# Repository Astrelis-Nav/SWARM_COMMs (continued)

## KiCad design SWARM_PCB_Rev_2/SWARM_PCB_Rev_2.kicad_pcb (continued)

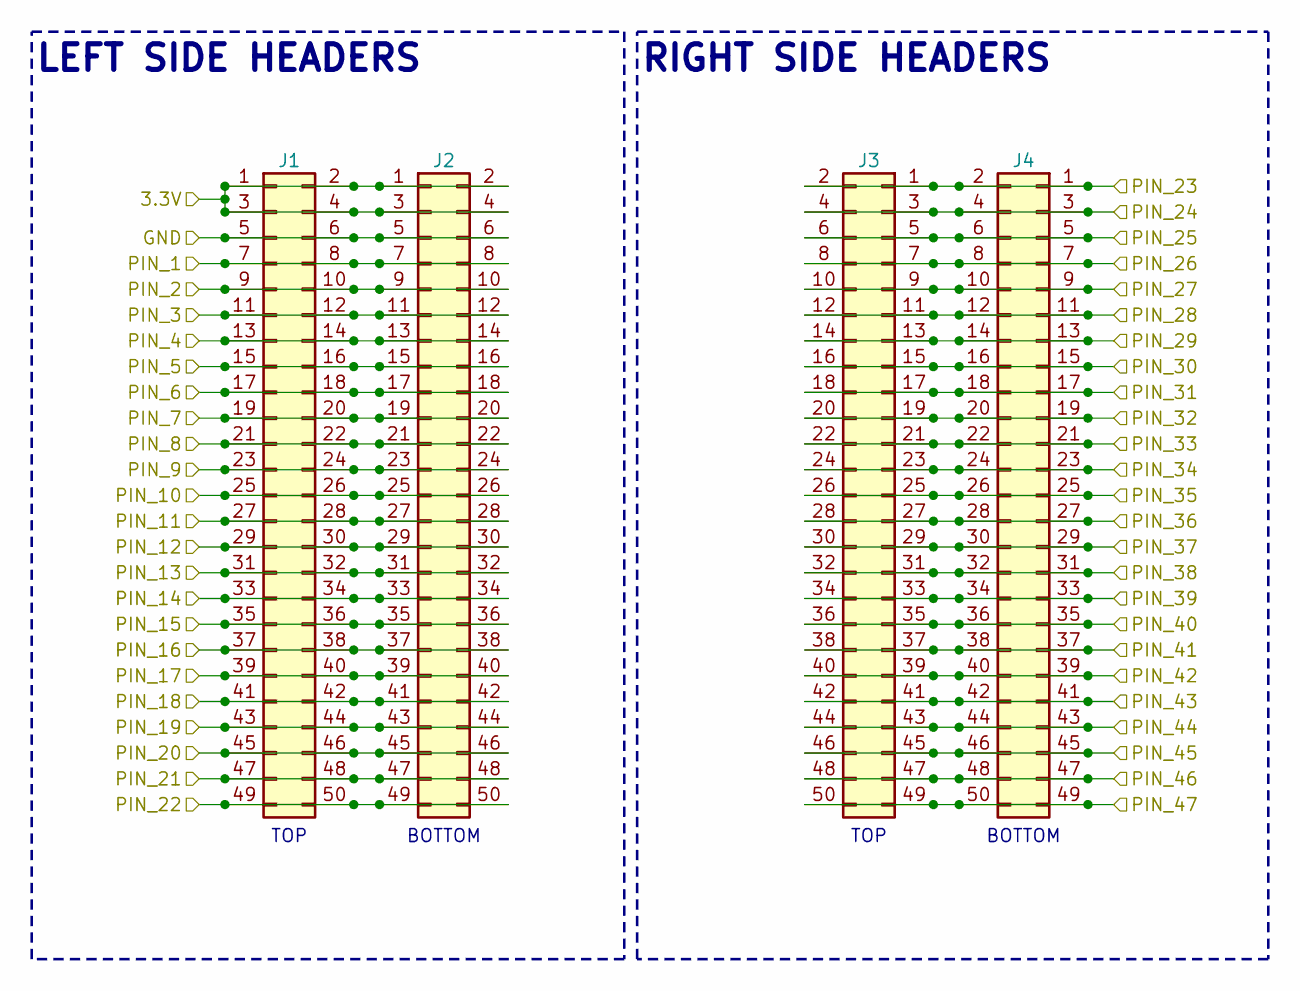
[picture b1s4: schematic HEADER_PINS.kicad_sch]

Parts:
J1: Conn_02x25_Odd_Even; HIROSE_DF40C-50DP-0.4V_51_
J2, J3, J4: Conn_02x25_Odd_Even; HIROSE_DF40C-50DP-0.4V_51_; MPN DF40C-50DP-0.4V(51)

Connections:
+3.3V_CONTROL: J1.1, J1.2, J1.3, J1.4, J2.1, J2.2, J2.3, J2.4; also elsewhere on the board
/CONTROL/ADC1_IN0: J3.45, J3.46, J4.45, J4.46; also elsewhere on the board
/CONTROL/ADC1_IN1: J3.47, J3.48, J4.47, J4.48; also elsewhere on the board
/CONTROL/ADC1_IN2: J3.49, J3.50, J4.49, J4.50; also elsewhere on the board
/CONTROL/ADC1_IN3: J3.37, J3.38, J4.37, J4.38; also elsewhere on the board
/CONTROL/GPIO_0: J3.1, J3.2, J4.1, J4.2; also elsewhere on the board
/CONTROL/GPIO_1: J3.3, J3.4, J4.3, J4.4; also elsewhere on the board
/CONTROL/GPIO_6: J3.5, J3.6, J4.5, J4.6; also elsewhere on the board
/CONTROL/GPIO_7: J3.7, J3.8, J4.7, J4.8; also elsewhere on the board
/CONTROL/GPIO_8: J3.9, J3.10, J4.9, J4.10; also elsewhere on the board
/CONTROL/GPIO_9: J3.11, J3.12, J4.11, J4.12; also elsewhere on the board
/CONTROL/GPIO_10: J3.13, J3.14, J4.13, J4.14; also elsewhere on the board
/CONTROL/GPIO_11: J3.15, J3.16, J4.15, J4.16; also elsewhere on the board
/CONTROL/GPIO_12: J3.17, J3.18, J4.17, J4.18; also elsewhere on the board
/CONTROL/GPIO_13: J3.19, J3.20, J4.19, J4.20; also elsewhere on the board
/CONTROL/GPIO_14: J3.21, J3.22, J4.21, J4.22; also elsewhere on the board
/CONTROL/GPIO_15: J3.23, J3.24, J4.23, J4.24; also elsewhere on the board
/CONTROL/GPIO_21: J1.39, J1.40, J2.39, J2.40; also elsewhere on the board
/CONTROL/GPIO_22: J1.13, J1.14, J2.13, J2.14; also elsewhere on the board
/CONTROL/GPIO_26: J1.11, J1.12, J2.11, J2.12; also elsewhere on the board
/CONTROL/GPIO_27: J1.9, J1.10, J2.9, J2.10; also elsewhere on the board
/CONTROL/GPIO_28: J1.7, J1.8, J2.7, J2.8; also elsewhere on the board
/CONTROL/HI_A: J3.27, J3.28, J4.27, J4.28; also elsewhere on the board
/CONTROL/HI_B: J1.49, J1.50, J2.49, J2.50; also elsewhere on the board
/CONTROL/LI_A: J3.25, J3.26, J4.25, J4.26; also elsewhere on the board
/CONTROL/LI_B: J1.33, J1.34, J2.33, J2.34; also elsewhere on the board
/CONTROL/PA9: J1.29, J1.30, J2.29, J2.30; also elsewhere on the board
/CONTROL/PA10: J1.31, J1.32, J2.31, J2.32; also elsewhere on the board
/CONTROL/PB0: J3.31, J3.32, J4.31, J4.32; also elsewhere on the board
/CONTROL/PB1: J3.29, J3.30, J4.29, J4.30; also elsewhere on the board
/CONTROL/PB5: J1.41, J1.42, J2.41, J2.42; also elsewhere on the board
/CONTROL/PB6: J1.43, J1.44, J2.43, J2.44; also elsewhere on the board
/CONTROL/PB12: J1.15, J1.16, J2.15, J2.16; also elsewhere on the board
/CONTROL/PB14: J1.17, J1.18, J2.17, J2.18; also elsewhere on the board
/CONTROL/PB15: J1.19, J1.20, J2.19, J2.20; also elsewhere on the board
/CONTROL/PC0: J3.41, J3.42, J4.41, J4.42; also elsewhere on the board
/CONTROL/PC3: J3.43, J3.44, J4.43, J4.44; also elsewhere on the board
/CONTROL/PC4: J3.35, J3.36, J4.35, J4.36; also elsewhere on the board
/CONTROL/PC5: J3.33, J3.34, J4.33, J4.34; also elsewhere on the board
/CONTROL/PC6: J1.21, J1.22, J2.21, J2.22; also elsewhere on the board
/CONTROL/PC7: J1.23, J1.24, J2.23, J2.24; also elsewhere on the board
/CONTROL/PC8: J1.25, J1.26, J2.25, J2.26; also elsewhere on the board
/CONTROL/PC9: J1.27, J1.28, J2.27, J2.28; also elsewhere on the board
/CONTROL/PC10: J1.35, J1.36, J2.35, J2.36; also elsewhere on the board
/CONTROL/PC11: J1.37, J1.38, J2.37, J2.38; also elsewhere on the board
/CONTROL/PC13: J3.39, J3.40, J4.39, J4.40; also elsewhere on the board
/CONTROL/SCL: J1.47, J1.48, J2.47, J2.48; also elsewhere on the board
/CONTROL/SDA: J1.45, J1.46, J2.45, J2.46; also elsewhere on the board
GND_CONTROL: J1.5, J1.6, J2.5, J2.6; also elsewhere on the board

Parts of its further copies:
J5, J9, J17, J21, J29: Conn_02x25_Odd_Even; HIROSE_DF40C-50DP-0.4V_51_
J6, J7, J8, J10, J11, J12, J18, J19, J20, J22, J23, J24, J30, J31, J32: Conn_02x25_Odd_Even; HIROSE_DF40C-50DP-0.4V_51_; MPN DF40C-50DP-0.4V(51)

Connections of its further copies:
+3.3V_HEADER: J21.1, J21.2, J21.3, J21.4, J22.1, J22.2, J22.3, J22.4; also elsewhere on the board
+3.3V_OUTPUT: J29.1, J29.2, J29.3, J29.4, J30.1, J30.2, J30.3, J30.4
+3.3V_POWER: J5.1, J5.2, J5.3, J5.4, J6.1, J6.2, J6.3, J6.4; also elsewhere on the board
+3.3V_SENSOR: J9.1, J9.2, J9.3, J9.4, J10.1, J10.2, J10.3, J10.4; also elsewhere on the board
+3.3V_TXRX: J17.1, J17.2, J17.3, J17.4, J18.1, J18.2, J18.3, J18.4; also elsewhere on the board
/ACC1_INT1: J23.31, J23.32, J24.31, J24.32; also elsewhere on the board
/ACC1_INT2: J23.33, J23.34, J24.33, J24.34; also elsewhere on the board
/ACC2_INT1: J23.35, J23.36, J24.35, J24.36; also elsewhere on the board
/ACC2_INT2: J23.39, J23.40, J24.39, J24.40; also elsewhere on the board
/ADC1_IN0: J23.45, J23.46, J24.45, J24.46; also elsewhere on the board
/ADC1_IN1: J23.47, J23.48, J24.47, J24.48; also elsewhere on the board
/ADC_CURRENT: J23.37, J23.38, J24.37, J24.38; also elsewhere on the board
/BPF_OUT: J23.49, J23.50, J24.49, J24.50; also elsewhere on the board
/GPIO_0: J23.1, J23.2, J24.1, J24.2; also elsewhere on the board
/GPIO_1: J23.3, J23.4, J24.3, J24.4; also elsewhere on the board
/GPIO_6: J23.5, J23.6, J24.5, J24.6; also elsewhere on the board
/GPIO_7: J23.7, J23.8, J24.7, J24.8; also elsewhere on the board
/GPIO_8: J23.9, J23.10, J24.9, J24.10; also elsewhere on the board
/GPIO_9: J23.11, J23.12, J24.11, J24.12; also elsewhere on the board
/GPIO_10: J23.13, J23.14, J24.13, J24.14; also elsewhere on the board
/GPIO_11: J23.15, J23.16, J24.15, J24.16; also elsewhere on the board
/GPIO_12: J23.17, J23.18, J24.17, J24.18; also elsewhere on the board
/GPIO_13: J23.19, J23.20, J24.19, J24.20; also elsewhere on the board
/GPIO_14: J23.21, J23.22, J24.21, J24.22; also elsewhere on the board
/GPIO_15: J23.23, J23.24, J24.23, J24.24; also elsewhere on the board
/GPIO_21: J21.39, J21.40, J22.39, J22.40; also elsewhere on the board
/GPIO_22: J21.13, J21.14, J22.13, J22.14; also elsewhere on the board
/GPIO_26: J21.11, J21.12, J22.11, J22.12; also elsewhere on the board
/GPIO_27: J21.9, J21.10, J22.9, J22.10; also elsewhere on the board
/GPIO_28: J21.7, J21.8, J22.7, J22.8; also elsewhere on the board
/HI_A: J23.27, J23.28, J24.27, J24.28; also elsewhere on the board
/HI_B: J21.49, J21.50, J22.49, J22.50; also elsewhere on the board
/LI_A: J23.25, J23.26, J24.25, J24.26; also elsewhere on the board
/LI_B: J21.33, J21.34, J22.33, J22.34; also elsewhere on the board
/OUTPUT/GPIO_0: J31.1, J31.2, J32.1, J32.2; also elsewhere on the board
/OUTPUT/GPIO_1: J31.3, J31.4, J32.3, J32.4; also elsewhere on the board
/OUTPUT/GPIO_6: J31.5, J31.6, J32.5, J32.6; also elsewhere on the board
/OUTPUT/GPIO_7: J31.7, J31.8, J32.7, J32.8; also elsewhere on the board
/OUTPUT/GPIO_8: J31.9, J31.10, J32.9, J32.10; also elsewhere on the board
/OUTPUT/GPIO_9: J31.11, J31.12, J32.11, J32.12; also elsewhere on the board
/OUTPUT/GPIO_13: J31.19, J31.20, J32.19, J32.20; also elsewhere on the board
/OUTPUT/GPIO_14: J31.21, J31.22, J32.21, J32.22; also elsewhere on the board
/OUTPUT/GPIO_15: J31.23, J31.24, J32.23, J32.24; also elsewhere on the board
/OUTPUT/GPIO_21: J29.39, J29.40, J30.39, J30.40; also elsewhere on the board
/OUTPUT/GPIO_22: J29.13, J29.14, J30.13, J30.14; also elsewhere on the board
/OUTPUT/GPIO_26: J29.11, J29.12, J30.11, J30.12; also elsewhere on the board
/OUTPUT/GPIO_27: J29.9, J29.10, J30.9, J30.10; also elsewhere on the board
/OUTPUT/GPIO_28: J29.7, J29.8, J30.7, J30.8; also elsewhere on the board
/OUTPUT/HEADER_PINS/PIN_5: J29.15, J29.16, J30.15, J30.16
/OUTPUT/HEADER_PINS/PIN_6: J29.17, J29.18, J30.17, J30.18
/OUTPUT/HEADER_PINS/PIN_7: J29.19, J29.20, J30.19, J30.20
/OUTPUT/HEADER_PINS/PIN_8: J29.21, J29.22, J30.21, J30.22
/OUTPUT/HEADER_PINS/PIN_9: J29.23, J29.24, J30.23, J30.24
/OUTPUT/HEADER_PINS/PIN_10: J29.25, J29.26, J30.25, J30.26
/OUTPUT/HEADER_PINS/PIN_11: J29.27, J29.28, J30.27, J30.28
/OUTPUT/HEADER_PINS/PIN_12: J29.29, J29.30, J30.29, J30.30
/OUTPUT/HEADER_PINS/PIN_13: J29.31, J29.32, J30.31, J30.32
/OUTPUT/HEADER_PINS/PIN_14: J29.33, J29.34, J30.33, J30.34
/OUTPUT/HEADER_PINS/PIN_15: J29.35, J29.36, J30.35, J30.36
/OUTPUT/HEADER_PINS/PIN_16: J29.37, J29.38, J30.37, J30.38
/OUTPUT/HEADER_PINS/PIN_18: J29.41, J29.42, J30.41, J30.42
/OUTPUT/HEADER_PINS/PIN_19: J29.43, J29.44, J30.43, J30.44
/OUTPUT/HEADER_PINS/PIN_20: J29.45, J29.46, J30.45, J30.46
/OUTPUT/HEADER_PINS/PIN_21: J29.47, J29.48, J30.47, J30.48
/OUTPUT/HEADER_PINS/PIN_22: J29.49, J29.50, J30.49, J30.50
/OUTPUT/HEADER_PINS/PIN_29: J31.13, J31.14, J32.13, J32.14
/OUTPUT/HEADER_PINS/PIN_30: J31.15, J31.16, J32.15, J32.16
/OUTPUT/HEADER_PINS/PIN_31: J31.17, J31.18, J32.17, J32.18
/OUTPUT/HEADER_PINS/PIN_35: J31.25, J31.26, J32.25, J32.26
/OUTPUT/HEADER_PINS/PIN_36: J31.27, J31.28, J32.27, J32.28
/OUTPUT/HEADER_PINS/PIN_37: J31.29, J31.30, J32.29, J32.30
/OUTPUT/HEADER_PINS/PIN_38: J31.31, J31.32, J32.31, J32.32
/OUTPUT/HEADER_PINS/PIN_39: J31.33, J31.34, J32.33, J32.34
/OUTPUT/HEADER_PINS/PIN_40: J31.35, J31.36, J32.35, J32.36
/OUTPUT/HEADER_PINS/PIN_41: J31.37, J31.38, J32.37, J32.38
/OUTPUT/HEADER_PINS/PIN_42: J31.39, J31.40, J32.39, J32.40
/OUTPUT/HEADER_PINS/PIN_43: J31.41, J31.42, J32.41, J32.42
/OUTPUT/HEADER_PINS/PIN_44: J31.43, J31.44, J32.43, J32.44
/OUTPUT/HEADER_PINS/PIN_45: J31.45, J31.46, J32.45, J32.46
/OUTPUT/HEADER_PINS/PIN_46: J31.47, J31.48, J32.47, J32.48
/OUTPUT/HEADER_PINS/PIN_47: J31.49, J31.50, J32.49, J32.50
/PA9: J21.29, J21.30, J22.29, J22.30; also elsewhere on the board
/PB5: J21.41, J21.42, J22.41, J22.42; also elsewhere on the board
/PB14: J21.17, J21.18, J22.17, J22.18; also elsewhere on the board
/PB15: J21.19, J21.20, J22.19, J22.20; also elsewhere on the board
/PC6: J21.21, J21.22, J22.21, J22.22; also elsewhere on the board
/PC7: J21.23, J21.24, J22.23, J22.24; also elsewhere on the board
/PC8: J21.25, J21.26, J22.25, J22.26; also elsewhere on the board
/PC9: J21.27, J21.28, J22.27, J22.28; also elsewhere on the board
/PC10: J21.35, J21.36, J22.35, J22.36; also elsewhere on the board
/PC11: J21.37, J21.38, J22.37, J22.38; also elsewhere on the board
/PG_3.3V: J21.43, J21.44, J22.43, J22.44; also elsewhere on the board
/PG_5V: J21.31, J21.32, J22.31, J22.32; also elsewhere on the board
/PG_12V: J21.15, J21.16, J22.15, J22.16; also elsewhere on the board
/PG_VPiezo: J23.29, J23.30, J24.29, J24.30; also elsewhere on the board
/POWER/HEADER_PINS/PIN_1: J5.7, J5.8, J6.7, J6.8
/POWER/HEADER_PINS/PIN_2: J5.9, J5.10, J6.9, J6.10
/POWER/HEADER_PINS/PIN_3: J5.11, J5.12, J6.11, J6.12
/POWER/HEADER_PINS/PIN_4: J5.13, J5.14, J6.13, J6.14
/POWER/HEADER_PINS/PIN_6: J5.17, J5.18, J6.17, J6.18
/POWER/HEADER_PINS/PIN_7: J5.19, J5.20, J6.19, J6.20
/POWER/HEADER_PINS/PIN_8: J5.21, J5.22, J6.21, J6.22
/POWER/HEADER_PINS/PIN_9: J5.23, J5.24, J6.23, J6.24
/POWER/HEADER_PINS/PIN_10: J5.25, J5.26, J6.25, J6.26
/POWER/HEADER_PINS/PIN_11: J5.27, J5.28, J6.27, J6.28
/POWER/HEADER_PINS/PIN_12: J5.29, J5.30, J6.29, J6.30
/POWER/HEADER_PINS/PIN_14: J5.33, J5.34, J6.33, J6.34
/POWER/HEADER_PINS/PIN_15: J5.35, J5.36, J6.35, J6.36
/POWER/HEADER_PINS/PIN_16: J5.37, J5.38, J6.37, J6.38
/POWER/HEADER_PINS/PIN_17: J5.39, J5.40, J6.39, J6.40
/POWER/HEADER_PINS/PIN_18: J5.41, J5.42, J6.41, J6.42
/POWER/HEADER_PINS/PIN_20: J5.45, J5.46, J6.45, J6.46
/POWER/HEADER_PINS/PIN_21: J5.47, J5.48, J6.47, J6.48
/POWER/HEADER_PINS/PIN_22: J5.49, J5.50, J6.49, J6.50
/POWER/HEADER_PINS/PIN_23: J7.1, J7.2, J8.1, J8.2
/POWER/HEADER_PINS/PIN_24: J7.3, J7.4, J8.3, J8.4
/POWER/HEADER_PINS/PIN_25: J7.5, J7.6, J8.5, J8.6
/POWER/HEADER_PINS/PIN_26: J7.7, J7.8, J8.7, J8.8
/POWER/HEADER_PINS/PIN_27: J7.9, J7.10, J8.9, J8.10
/POWER/HEADER_PINS/PIN_28: J7.11, J7.12, J8.11, J8.12
/POWER/HEADER_PINS/PIN_29: J7.13, J7.14, J8.13, J8.14
/POWER/HEADER_PINS/PIN_30: J7.15, J7.16, J8.15, J8.16
/POWER/HEADER_PINS/PIN_31: J7.17, J7.18, J8.17, J8.18
/POWER/HEADER_PINS/PIN_32: J7.19, J7.20, J8.19, J8.20
/POWER/HEADER_PINS/PIN_33: J7.21, J7.22, J8.21, J8.22
/POWER/HEADER_PINS/PIN_34: J7.23, J7.24, J8.23, J8.24
/POWER/HEADER_PINS/PIN_35: J7.25, J7.26, J8.25, J8.26
/POWER/HEADER_PINS/PIN_36: J7.27, J7.28, J8.27, J8.28
/POWER/HEADER_PINS/PIN_38: J7.31, J7.32, J8.31, J8.32
/POWER/HEADER_PINS/PIN_39: J7.33, J7.34, J8.33, J8.34
/POWER/HEADER_PINS/PIN_40: J7.35, J7.36, J8.35, J8.36
/POWER/HEADER_PINS/PIN_41: J7.37, J7.38, J8.37, J8.38
/POWER/HEADER_PINS/PIN_42: J7.39, J7.40, J8.39, J8.40
/POWER/HEADER_PINS/PIN_43: J7.41, J7.42, J8.41, J8.42
/POWER/HEADER_PINS/PIN_44: J7.43, J7.44, J8.43, J8.44
/POWER/HEADER_PINS/PIN_45: J7.45, J7.46, J8.45, J8.46
/POWER/HEADER_PINS/PIN_46: J7.47, J7.48, J8.47, J8.48
/POWER/HEADER_PINS/PIN_47: J7.49, J7.50, J8.49, J8.50
/POWER/PG_3.3V: J5.43, J5.44, J6.43, J6.44; also elsewhere on the board
/POWER/PG_5V: J5.31, J5.32, J6.31, J6.32; also elsewhere on the board
/POWER/PG_12V: J5.15, J5.16, J6.15, J6.16; also elsewhere on the board
/POWER/PG_VPiezo: J7.29, J7.30, J8.29, J8.30; also elsewhere on the board
/RX_EN: J23.43, J23.44, J24.43, J24.44; also elsewhere on the board
/RX_FAULT: J23.41, J23.42, J24.41, J24.42; also elsewhere on the board
/SCL: J21.47, J21.48, J22.47, J22.48; also elsewhere on the board
/SDA: J21.45, J21.46, J22.45, J22.46; also elsewhere on the board
/SENSOR/ACC1_INT1: J11.31, J11.32, J12.31, J12.32; also elsewhere on the board
/SENSOR/ACC1_INT2: J11.33, J11.34, J12.33, J12.34; also elsewhere on the board
/SENSOR/ACC2_INT1: J11.35, J11.36, J12.35, J12.36; also elsewhere on the board
/SENSOR/ACC2_INT2: J11.39, J11.40, J12.39, J12.40; also elsewhere on the board
/SENSOR/HEADER_PINS/PIN_1: J9.7, J9.8, J10.7, J10.8
/SENSOR/HEADER_PINS/PIN_2: J9.9, J9.10, J10.9, J10.10
/SENSOR/HEADER_PINS/PIN_3: J9.11, J9.12, J10.11, J10.12
/SENSOR/HEADER_PINS/PIN_4: J9.13, J9.14, J10.13, J10.14
/SENSOR/HEADER_PINS/PIN_5: J9.15, J9.16, J10.15, J10.16
/SENSOR/HEADER_PINS/PIN_6: J9.17, J9.18, J10.17, J10.18
/SENSOR/HEADER_PINS/PIN_7: J9.19, J9.20, J10.19, J10.20
/SENSOR/HEADER_PINS/PIN_8: J9.21, J9.22, J10.21, J10.22
/SENSOR/HEADER_PINS/PIN_9: J9.23, J9.24, J10.23, J10.24
/SENSOR/HEADER_PINS/PIN_10: J9.25, J9.26, J10.25, J10.26
/SENSOR/HEADER_PINS/PIN_11: J9.27, J9.28, J10.27, J10.28
/SENSOR/HEADER_PINS/PIN_12: J9.29, J9.30, J10.29, J10.30
/SENSOR/HEADER_PINS/PIN_13: J9.31, J9.32, J10.31, J10.32
/SENSOR/HEADER_PINS/PIN_14: J9.33, J9.34, J10.33, J10.34
/SENSOR/HEADER_PINS/PIN_15: J9.35, J9.36, J10.35, J10.36
/SENSOR/HEADER_PINS/PIN_16: J9.37, J9.38, J10.37, J10.38
/SENSOR/HEADER_PINS/PIN_17: J9.39, J9.40, J10.39, J10.40
/SENSOR/HEADER_PINS/PIN_18: J9.41, J9.42, J10.41, J10.42
/SENSOR/HEADER_PINS/PIN_19: J9.43, J9.44, J10.43, J10.44
/SENSOR/HEADER_PINS/PIN_22: J9.49, J9.50, J10.49, J10.50
/SENSOR/HEADER_PINS/PIN_23: J11.1, J11.2, J12.1, J12.2
/SENSOR/HEADER_PINS/PIN_24: J11.3, J11.4, J12.3, J12.4
/SENSOR/HEADER_PINS/PIN_25: J11.5, J11.6, J12.5, J12.6
/SENSOR/HEADER_PINS/PIN_26: J11.7, J11.8, J12.7, J12.8
/SENSOR/HEADER_PINS/PIN_27: J11.9, J11.10, J12.9, J12.10
/SENSOR/HEADER_PINS/PIN_28: J11.11, J11.12, J12.11, J12.12
/SENSOR/HEADER_PINS/PIN_29: J11.13, J11.14, J12.13, J12.14
/SENSOR/HEADER_PINS/PIN_30: J11.15, J11.16, J12.15, J12.16
/SENSOR/HEADER_PINS/PIN_31: J11.17, J11.18, J12.17, J12.18
/SENSOR/HEADER_PINS/PIN_32: J11.19, J11.20, J12.19, J12.20
/SENSOR/HEADER_PINS/PIN_33: J11.21, J11.22, J12.21, J12.22
/SENSOR/HEADER_PINS/PIN_34: J11.23, J11.24, J12.23, J12.24
/SENSOR/HEADER_PINS/PIN_35: J11.25, J11.26, J12.25, J12.26
/SENSOR/HEADER_PINS/PIN_36: J11.27, J11.28, J12.27, J12.28
/SENSOR/HEADER_PINS/PIN_37: J11.29, J11.30, J12.29, J12.30
/SENSOR/HEADER_PINS/PIN_41: J11.37, J11.38, J12.37, J12.38
/SENSOR/HEADER_PINS/PIN_43: J11.41, J11.42, J12.41, J12.42
/SENSOR/HEADER_PINS/PIN_44: J11.43, J11.44, J12.43, J12.44
/SENSOR/HEADER_PINS/PIN_45: J11.45, J11.46, J12.45, J12.46
/SENSOR/HEADER_PINS/PIN_46: J11.47, J11.48, J12.47, J12.48
/SENSOR/HEADER_PINS/PIN_47: J11.49, J11.50, J12.49, J12.50
/SENSOR/SCL: J9.47, J9.48, J10.47, J10.48; also elsewhere on the board
/SENSOR/SDA: J9.45, J9.46, J10.45, J10.46; also elsewhere on the board
/TX_RX/ADC_CURRENT: J19.37, J19.38, J20.37, J20.38; also elsewhere on the board
/TX_RX/BPF_OUT: J19.49, J19.50, J20.49, J20.50; also elsewhere on the board
/TX_RX/HEADER_PINS/PIN_1: J17.7, J17.8, J18.7, J18.8
/TX_RX/HEADER_PINS/PIN_2: J17.9, J17.10, J18.9, J18.10
/TX_RX/HEADER_PINS/PIN_3: J17.11, J17.12, J18.11, J18.12
/TX_RX/HEADER_PINS/PIN_4: J17.13, J17.14, J18.13, J18.14
/TX_RX/HEADER_PINS/PIN_5: J17.15, J17.16, J18.15, J18.16
/TX_RX/HEADER_PINS/PIN_6: J17.17, J17.18, J18.17, J18.18
/TX_RX/HEADER_PINS/PIN_7: J17.19, J17.20, J18.19, J18.20
/TX_RX/HEADER_PINS/PIN_8: J17.21, J17.22, J18.21, J18.22
/TX_RX/HEADER_PINS/PIN_9: J17.23, J17.24, J18.23, J18.24
/TX_RX/HEADER_PINS/PIN_10: J17.25, J17.26, J18.25, J18.26
/TX_RX/HEADER_PINS/PIN_11: J17.27, J17.28, J18.27, J18.28
/TX_RX/HEADER_PINS/PIN_12: J17.29, J17.30, J18.29, J18.30
/TX_RX/HEADER_PINS/PIN_13: J17.31, J17.32, J18.31, J18.32
/TX_RX/HEADER_PINS/PIN_15: J17.35, J17.36, J18.35, J18.36
/TX_RX/HEADER_PINS/PIN_16: J17.37, J17.38, J18.37, J18.38
/TX_RX/HEADER_PINS/PIN_17: J17.39, J17.40, J18.39, J18.40
/TX_RX/HEADER_PINS/PIN_18: J17.41, J17.42, J18.41, J18.42
/TX_RX/HEADER_PINS/PIN_19: J17.43, J17.44, J18.43, J18.44
/TX_RX/HEADER_PINS/PIN_20: J17.45, J17.46, J18.45, J18.46
/TX_RX/HEADER_PINS/PIN_21: J17.47, J17.48, J18.47, J18.48
/TX_RX/HEADER_PINS/PIN_23: J19.1, J19.2, J20.1, J20.2
/TX_RX/HEADER_PINS/PIN_24: J19.3, J19.4, J20.3, J20.4
/TX_RX/HEADER_PINS/PIN_25: J19.5, J19.6, J20.5, J20.6
/TX_RX/HEADER_PINS/PIN_26: J19.7, J19.8, J20.7, J20.8
/TX_RX/HEADER_PINS/PIN_27: J19.9, J19.10, J20.9, J20.10
/TX_RX/HEADER_PINS/PIN_28: J19.11, J19.12, J20.11, J20.12
/TX_RX/HEADER_PINS/PIN_29: J19.13, J19.14, J20.13, J20.14
/TX_RX/HEADER_PINS/PIN_30: J19.15, J19.16, J20.15, J20.16
/TX_RX/HEADER_PINS/PIN_31: J19.17, J19.18, J20.17, J20.18
/TX_RX/HEADER_PINS/PIN_32: J19.19, J19.20, J20.19, J20.20
/TX_RX/HEADER_PINS/PIN_33: J19.21, J19.22, J20.21, J20.22
/TX_RX/HEADER_PINS/PIN_34: J19.23, J19.24, J20.23, J20.24
/TX_RX/HEADER_PINS/PIN_37: J19.29, J19.30, J20.29, J20.30
/TX_RX/HEADER_PINS/PIN_38: J19.31, J19.32, J20.31, J20.32
/TX_RX/HEADER_PINS/PIN_39: J19.33, J19.34, J20.33, J20.34
/TX_RX/HEADER_PINS/PIN_40: J19.35, J19.36, J20.35, J20.36
/TX_RX/HEADER_PINS/PIN_42: J19.39, J19.40, J20.39, J20.40
/TX_RX/HEADER_PINS/PIN_45: J19.45, J19.46, J20.45, J20.46
/TX_RX/HEADER_PINS/PIN_46: J19.47, J19.48, J20.47, J20.48
/TX_RX/HI_A: J19.27, J19.28, J20.27, J20.28; also elsewhere on the board
/TX_RX/HI_B: J17.49, J17.50, J18.49, J18.50; also elsewhere on the board
/TX_RX/LI_A: J19.25, J19.26, J20.25, J20.26; also elsewhere on the board
/TX_RX/LI_B: J17.33, J17.34, J18.33, J18.34; also elsewhere on the board
/TX_RX/RX_EN: J19.43, J19.44, J20.43, J20.44; also elsewhere on the board
/TX_RX/RX_FAULT: J19.41, J19.42, J20.41, J20.42; also elsewhere on the board
GND_HEADER: J21.5, J21.6, J22.5, J22.6; also elsewhere on the board
GND_OUTPUT: J29.5, J29.6, J30.5, J30.6; also elsewhere on the board
GND_POWER: J5.5, J5.6, J6.5, J6.6; also elsewhere on the board
GND_SENSOR: J9.5, J9.6, J10.5, J10.6; also elsewhere on the board
GND_TXRX: J17.5, J17.6, J18.5, J18.6; also elsewhere on the board

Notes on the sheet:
BOTTOM
TOP
RIGHT SIDE HEADERS
LEFT SIDE HEADERS

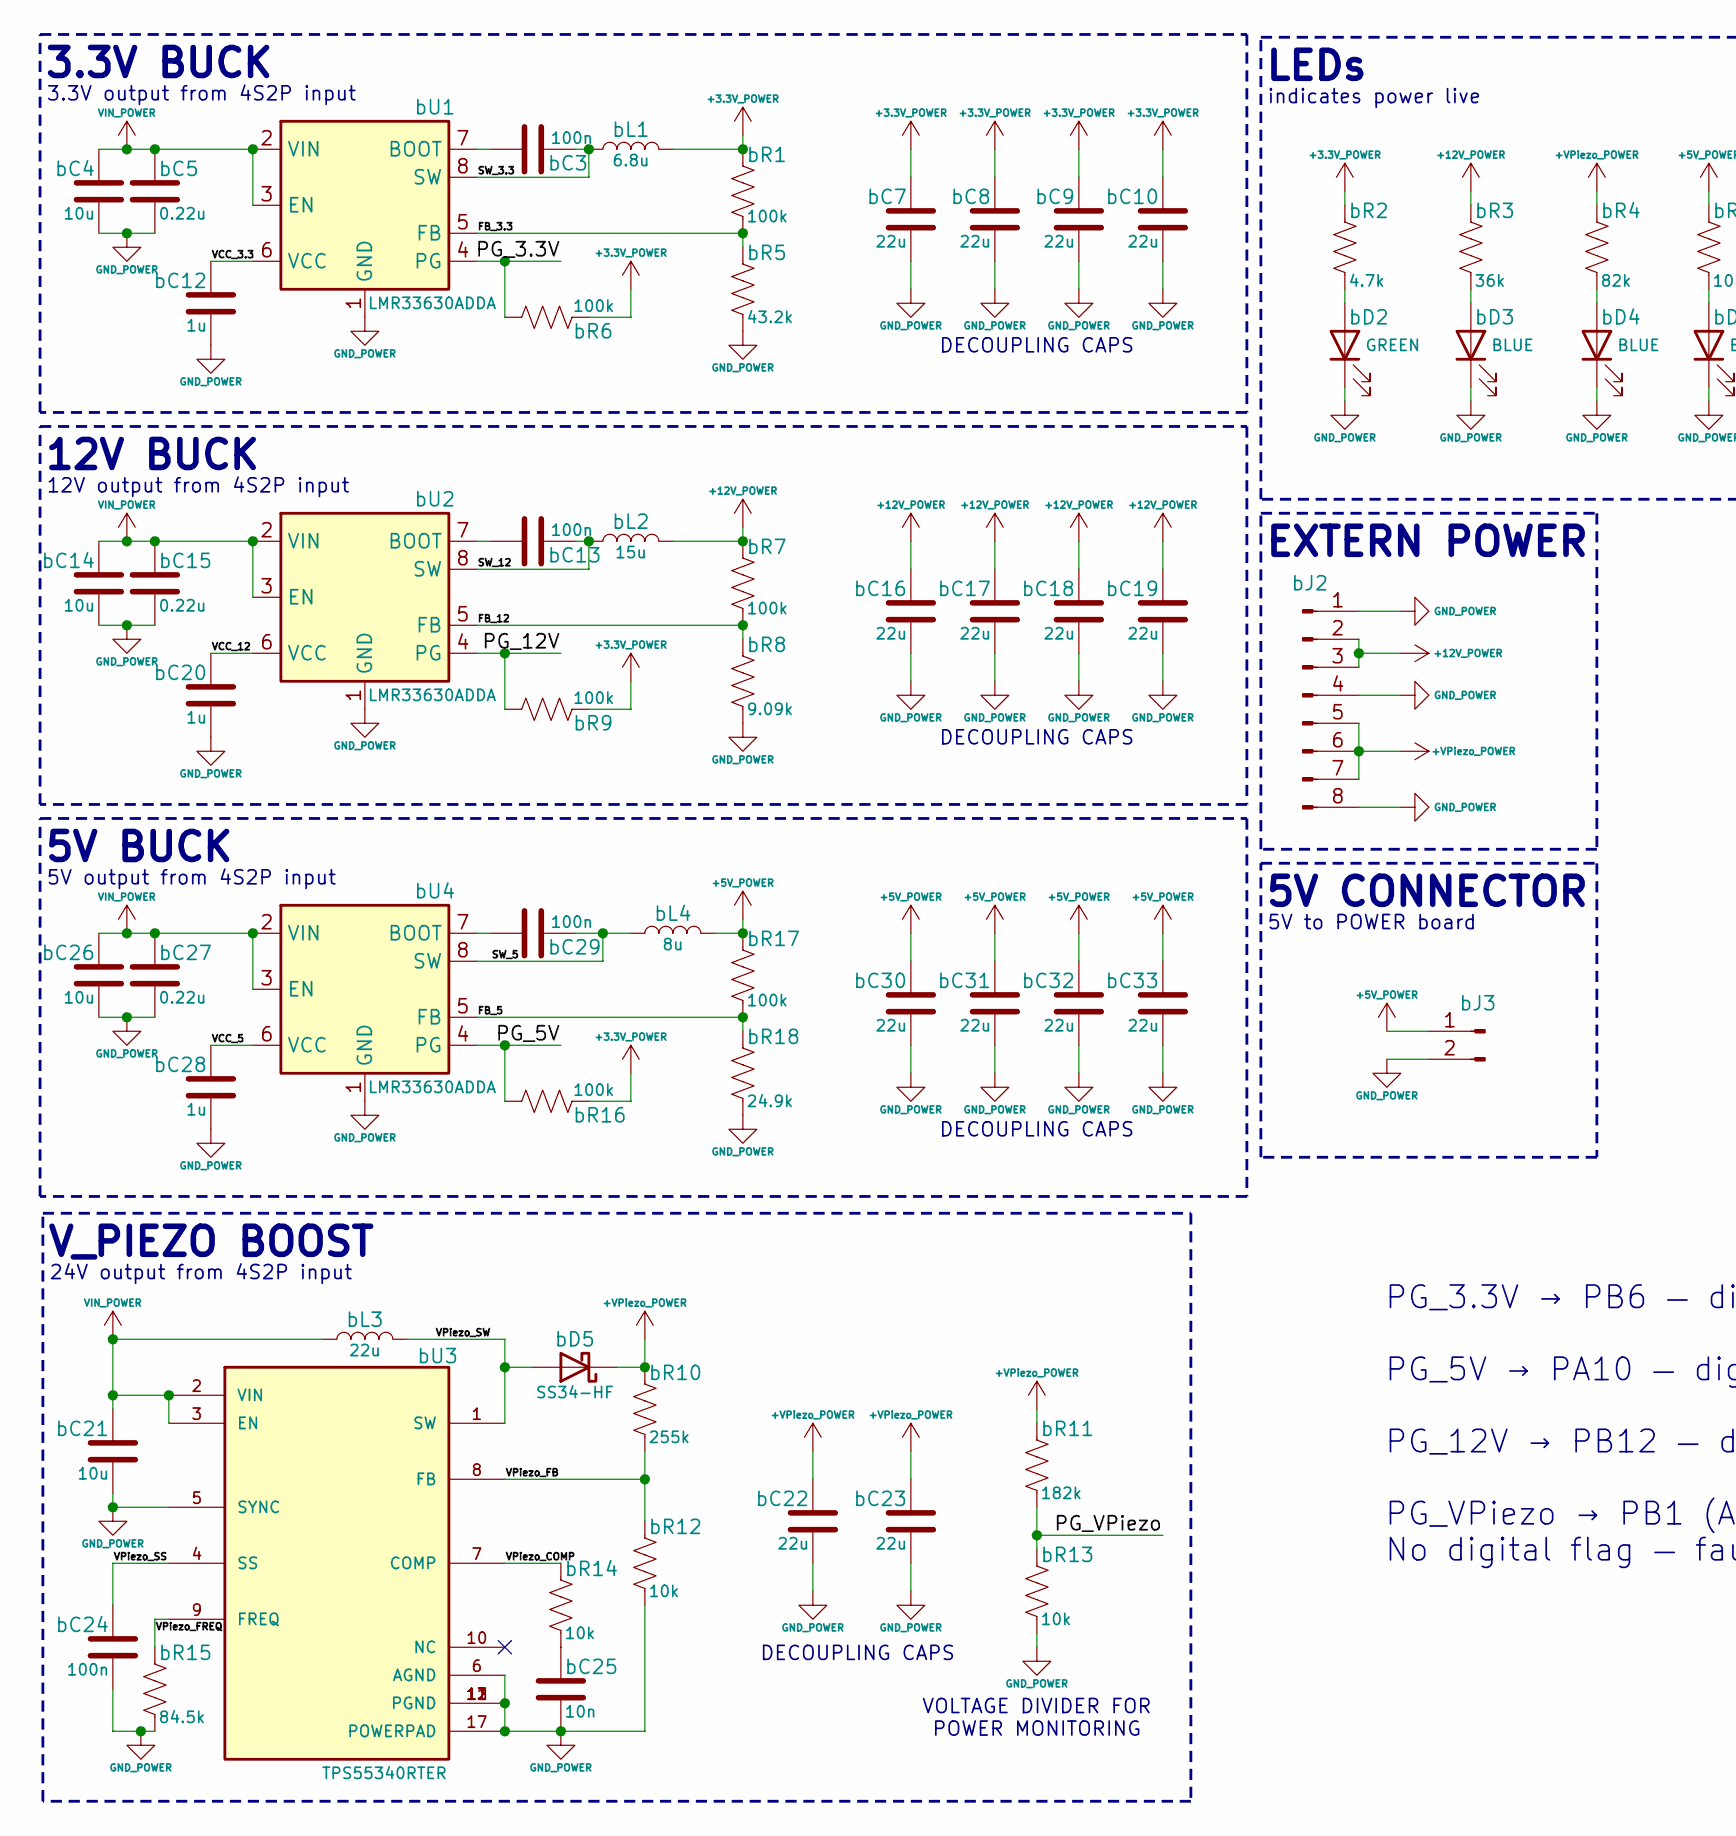
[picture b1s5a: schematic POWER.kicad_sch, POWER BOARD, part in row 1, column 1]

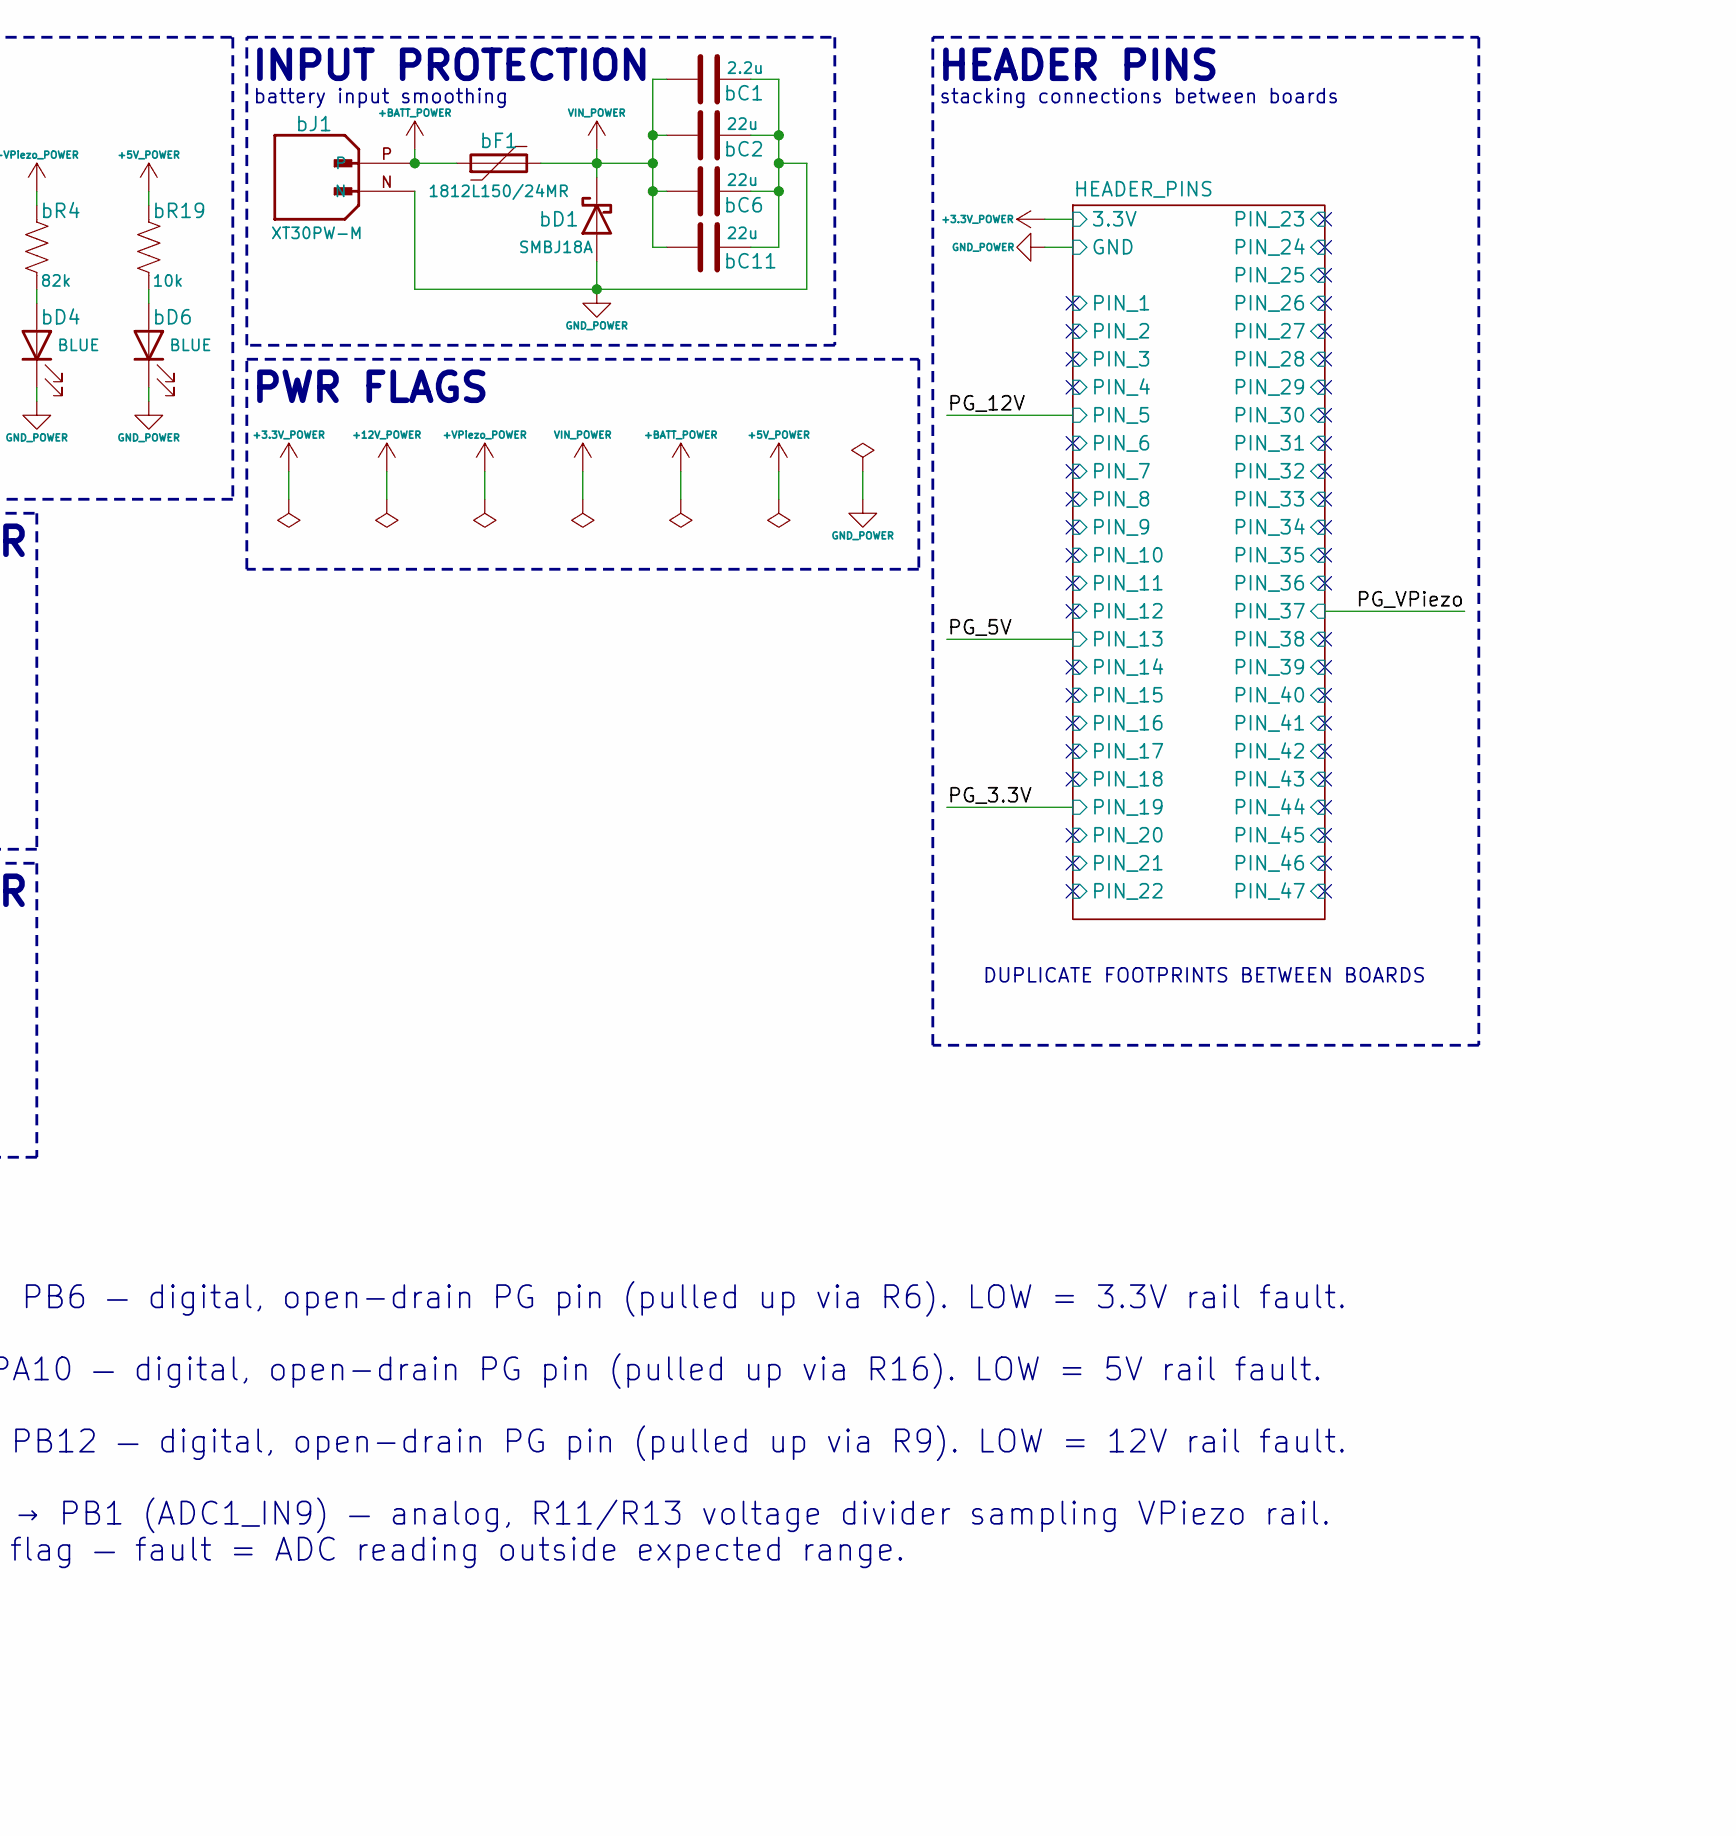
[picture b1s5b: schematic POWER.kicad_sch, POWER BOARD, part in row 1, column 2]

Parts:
bC1: 2.2u; C_0805_2012Metric; MPN GRM21BR71H225KA12L
bC2, bC6, bC11, bC22, bC23: 22u; C_1210_3225Metric; MPN GRM32ER61H226KE15L
bC3, bC13, bC24, bC29: 100n; C_0603_1608Metric; MPN GRM188R71C104KA01D
bC4, bC14, bC21, bC26: 10u; C_0805_2012Metric; MPN GRM21BR71H106KA73L
bC5, bC15, bC27: 0.22u; C_0603_1608Metric; MPN GRM21BR71H224KA73L
bC7, bC8, bC9, bC10, bC16, bC17, bC18, bC19, bC30, bC31, bC32, bC33: 22u; C_0805_2012Metric; MPN GRM21BR61E226ME11L
bC12, bC20, bC28: 1u; C_0603_1608Metric; MPN GRM188R61A105KA61D
bC25: 10n; C_0603_1608Metric; MPN GRM188R71H103KA01D
bD1: SMBJ18A; D_SMB; MPN SMBJ18A
bD2: GREEN; LED_JE2835_CRW
bD3, bD4, bD6: BLUE; LED_JE2835_CRW
bD5: SS34-HF; D_SMA; MPN SS34-HF
bF1: 1812L150/24MR; Fuse_1812_4532Metric; MPN 1812L150/24MR
bJ1: XT30PW-M; AMASS_XT30PW-M; PARTREV 1.2
bJ2: Conn_01x08_Pin; JST_PH_B8B-PH-SM4-TB_1x08-1MP_P2.00mm_Vertical; MPN B8B-PH-SM4-TB(LF)(SN)
bJ3: Conn_01x02_Pin; JST_PH_B2B-PH-SM4-TB_1x02-1MP_P2.00mm_Vertical
bL1: 6.8u; L_Wuerth_MAPI-5030; MPN 7447799068
bL2: 15u; L_Wuerth_MAPI-5030; MPN 7447799150
bL3: 22u; L_Panasonic_PCC-M0630M; MPN ETQP6M220YGC
bL4: 8u; L_Wuerth_MAPI-5030; MPN 7447799068
bR1, bR6, bR7, bR9, bR16, bR17: 100k; R_0603_1608Metric; MPN RC0603FR-07100KL
bR2: 4.7k; R_0603_1608Metric; MPN RC0603FR-074K7L
bR3: 36k; R_0603_1608Metric; MPN RC0603FR-0736KL
bR4: 82k; R_0603_1608Metric; MPN RC0603FR-0782KL
bR5: 43.2k; R_0603_1608Metric; MPN RC0603FR-0743K2L
bR8: 9.09k; R_0603_1608Metric; MPN RC0603FR-079K09L
bR10: 255k; R_0603_1608Metric; MPN RC0603FR-07255KL
bR11: 182k; R_0603_1608Metric; MPN RC0603FR-07182KL
bR12, bR13, bR14: 10k; R_0603_1608Metric; MPN RC0603FR-0710KL
bR15: 84.5k; R_0603_1608Metric; MPN RC0603FR-0784K5L
bR18: 24.9k; R_0603_1608Metric; MPN RC0603FR-0743K2L
bR19: 10k; R_0603_1608Metric; MPN RC0603FR-0782KL
bU1, bU2, bU4: LMR33630ADDA; Texas_HSOP-8-1EP_3.9x4.9mm_P1.27mm_ThermalVias; MPN LMR33630ADDA
bU3: TPS55340RTER; QFN50P300X300X80-17N; MPN TPS55340RTER

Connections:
+3.3V_POWER: bC7.2, bC8.2, bC9.2, bC10.2, bL1.2, bR1.2, bR2.2, bR6.1, bR9.1, bR16.1; also elsewhere on the board
+5V_POWER: bC30.2, bC31.2, bC32.2, bC33.2, bJ3.1, bL4.2, bR17.2, bR19.2
+12V_POWER: bC16.2, bC17.2, bC18.2, bC19.2, bJ2.2, bJ2.3, bL2.2, bR3.2, bR7.2
+BATT_POWER: bF1.1, bJ1.P
+VPiezo_POWER: bC22.2, bC23.2, bD5.1 (K), bJ2.5, bJ2.6, bJ2.7, bR4.2, bR10.2, bR11.2
/POWER/FB_3.3: bR1.1, bR5.2, bU1.5 (FB)
/POWER/FB_5: bR17.1, bR18.2, bU4.5 (FB)
/POWER/FB_12: bR7.1, bR8.2, bU2.5 (FB)
/POWER/PG_3.3V: bR6.2, bU1.4 (PG); also elsewhere on the board
/POWER/PG_5V: bR16.2, bU4.4 (PG); also elsewhere on the board
/POWER/PG_12V: bR9.2, bU2.4 (PG); also elsewhere on the board
/POWER/PG_VPiezo: bR11.1, bR13.2; also elsewhere on the board
/POWER/SW_3.3: bC3.2, bL1.1, bU1.8 (SW)
/POWER/SW_5: bC29.2, bL4.1, bU4.8 (SW)
/POWER/SW_12: bC13.2, bL2.1, bU2.8 (SW)
/POWER/VCC_3.3: bC12.2, bU1.6 (VCC)
/POWER/VCC_5: bC28.2, bU4.6 (VCC)
/POWER/VCC_12: bC20.2, bU2.6 (VCC)
/POWER/VPiezo_COMP: bR14.2, bU3.7 (COMP)
/POWER/VPiezo_FB: bR10.1, bR12.2, bU3.8 (FB)
/POWER/VPiezo_FREQ: bR15.2, bU3.9 (FREQ)
/POWER/VPiezo_SS: bC24.2, bU3.4 (SS)
/POWER/VPiezo_SW: bD5.2 (A), bL3.2, bU3.1 (SW), bU3.15 (SW), bU3.16 (SW)
GND_POWER: bC1.2, bC2.2, bC4.1, bC5.1, bC6.2, bC7.1, bC8.1, bC9.1, bC10.1, bC11.2, bC12.1, bC14.1, bC15.1, bC16.1, bC17.1, bC18.1, bC19.1, bC20.1, bC21.1, bC22.1, bC23.1, bC24.1, bC25.1, bC26.1, bC27.1, bC28.1, bC30.1, bC31.1, bC32.1, bC33.1, bD1.2 (A), bD2.1 (K), bD3.1 (K), bD4.1 (K), bD6.1 (K), bJ1.N, bJ2.1, bJ2.4, bJ2.8, bJ3.2, bR5.1, bR8.1, bR12.1, bR13.1, bR15.1, bR18.1, bU1.1 (GND), bU1.9 (GND), bU2.1 (GND), bU2.9 (GND), bU3.5 (SYNC), bU3.6 (AGND), bU3.11 (PGND), bU3.12 (PGND), bU3.13 (PGND), bU3.17 (POWERPAD), bU4.1 (GND), bU4.9 (GND); also elsewhere on the board
unnamed: bC25.2, bR14.1
unnamed: bD2.2 (A), bR2.1
unnamed: bD3.2 (A), bR3.1
unnamed: bD4.2 (A), bR4.1
unnamed: bD6.2 (A), bR19.1
unnamed: bC3.1, bU1.7 (BOOT)
unnamed: bC13.1, bU2.7 (BOOT)
unnamed: bC29.1, bU4.7 (BOOT)
VIN_POWER: bC1.1, bC2.1, bC4.2, bC5.2, bC6.1, bC11.1, bC14.2, bC15.2, bC21.2, bC26.2, bC27.2, bD1.1 (K), bF1.2, bL3.1, bU1.2 (VIN), bU1.3 (EN), bU2.2 (VIN), bU2.3 (EN), bU3.2 (VIN), bU3.3 (EN), bU4.2 (VIN), bU4.3 (EN)

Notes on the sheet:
DECOUPLING CAPS
3.3V BUCK
24V output from 4S2P input
DUPLICATE FOOTPRINTS BETWEEN BOARDS
HEADER PINS
indicates power live
5V CONNECTOR
5V to POWER board
VOLTAGE DIVIDER FOR POWER MONITORING
LEDs
12V BUCK
5V output from 4S2P input
battery input smoothing
PWR FLAGS
PG_3.3V → PB6 — digital, open-drain PG pin (pulled up via R6). LOW = 3.3V rail fault. PG_5V → PA10 — digital, open-drain PG pin (pulled up via R16). LOW = 5V rail fault. PG_12V → PB12 — digital, open-drain PG pin (pulled up via R9). LOW = 12V rail fault. PG_VPiezo → PB1 (ADC1_IN9) — analog, R11/R13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
INPUT PROTECTION
12V output from 4S2P input
5V BUCK
3.3V output from 4S2P input
stacking connections between boards
V_PIEZO BOOST
EXTERN POWER
